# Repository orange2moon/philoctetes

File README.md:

# Philoctetes Keyboard

## About this project

I have worked on this project for about 3 months. It is quite enjoyable, but also time consuming. I made two working keyboards, one bluetooth and one wireless. The feel of the layout is fantastic! Even if my keyboards are working, it's not ready for other people to build. I hope to have time to continue this project, but I can't make promises to anyone. I am sharing this repository for people who might be curious, and to give ideas so as to inspire people to make awesome keyboards.

__Design goals__  
In [congnitive load theory](https://practicalpie.com/cognitive-load-theory/) there are three processes. These are the intrinsic, the extrinsic, and the germane. The effort put into typing on a keyboard is purely extrinsic. So one day I had an idea, "could I reduce the extrinsic load of typing on a computer by changing my keyboard?". I think the answer is yes. As a result of this idea, my design goals gravitated toward 42 keys that are arranged to match my hand and the movements of my fingers.

This keyboard turned into a very expensive build. It is probably one of the most expensive split keyboards you can build. In addition I only considered the shape and size of my own hand when designing it. Please don't build it.

## Other Projects to Check Out

The [Totem](https://github.com/GEIGEIGEIST/TOTEM) keyboard. The Totem was the inspiration for this keyboard. I have huge respect for the creator of this project. The creator really put a lot of effort into making a great finished project.

I created this project with a different design goal in mind. The design goals of the Totem seem to be a portable and relativly low cost keyboard. In contrast, my design goals are to fit perfectly my own hand.

In addition, a big thanks to the [EIGA](https://www.youtube.com/@EIGAtech) youtube channel. Without their channel I would not have learned about the Totem and other split keyboards.

## To Do

__Case__  
[x] Add a case mount point to the far outside.  
[x] Add more space for the oled (the oled is not centered and it hits the lip holding the cover). Moving the oled mount half a mm towards the edge should help.  
[x] Add more space for the microcontroller (about 1mm on the inner side should do).  
[x] Add a curve for the TRRS conector.  

__PCB Both Sides__  
[x] fix the annotations  
[] change the footprints from sod-323 to sod-123.  
    - The Kicad library footprints look too small for hand soldering.  
[] Update the footprints in the PCB builder.  
[] Redo diode placement  
[] Redo routing  
[] Improve the silkscreen placements.  
[x] Improve the placement of the oled display.  
[x] Add a case mount point to the far outside.  
[x] Add a pull down resistor to the right side.  
[x] Remove the extra diode on the left side.  
[x] Panelize the keyboard.  
[x] Check the column and row labels and makes sure they match.  
[x] Check the oled and nice!view pinouts.  
  
__Project In General__  
[] Create a bill of materials  
[] Create a build guide  
[] Test latest PCB  
  
## Case  
  
The case uses a tenting system that I have used for a year. It's not perfect, but every-time I think of switching to a different design I can't find justification. The advantage of my tenting system is that it is very stable and very adjustable. My tenting system is not portable, meaning it will probably bet messed up if you put it in a bag and ride the subway (been there, done that).  
  
The case was designed using onshape and you can find a link to it [here](https://cad.onshape.com/documents/5c5e04ae1784123d6189c14c/w/86f29d74e9109abb974cb649/e/b3c51a35815c88e0a251e0eb?renderMode=0&uiState=679c96c15b955f7398b0b3b0)  

## Images

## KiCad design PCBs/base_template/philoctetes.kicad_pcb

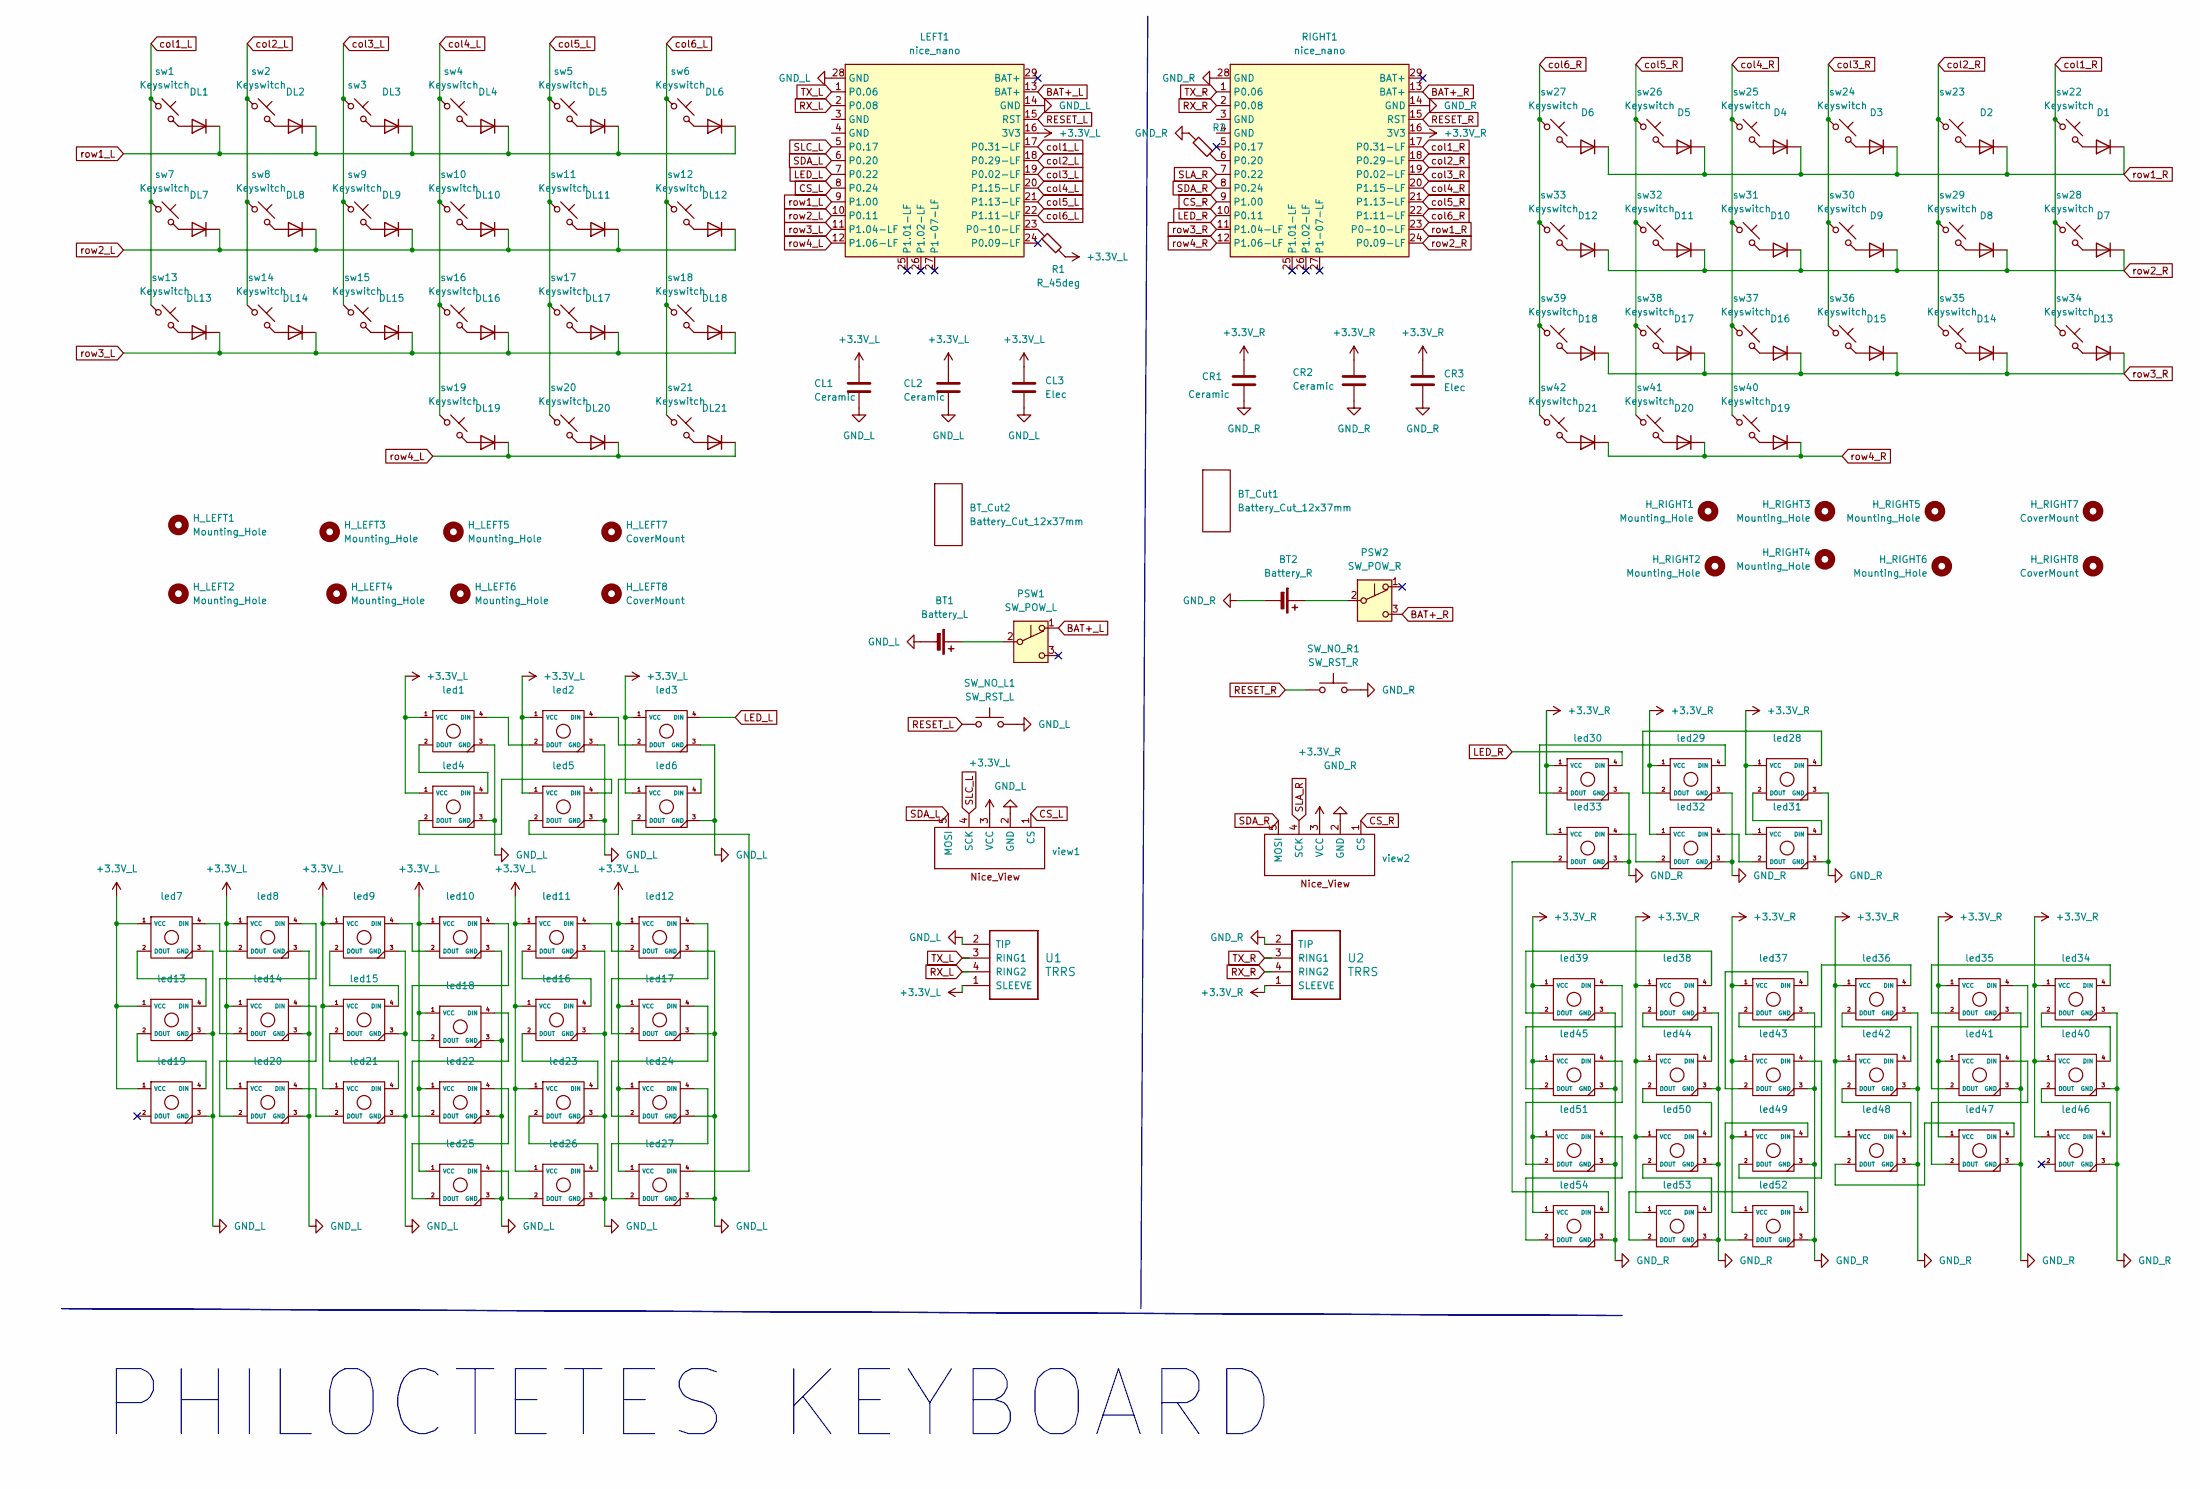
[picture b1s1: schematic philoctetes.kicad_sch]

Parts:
BT1: Battery_L; JST_GH_SM02B-GHS-TB_1x02-1MP_P1.25mm_Horizontal
BT2: Battery_R; JST_GH_SM02B-GHS-TB_1x02-1MP_P1.25mm_Horizontal
BT_Cut1, BT_Cut2: Battery_Cut_12x37mm
CL1, CL2: Ceramic; C_1206_3216Metric_Pad1.33x1.80mm_HandSolder
CL3: Elec; CP_Radial_D5.0mm_P2.00mm
CR1, CR2: Ceramic; C_1206_3216Metric_Pad1.33x1.80mm_HandSolder
CR3: Elec; CP_Radial_D5.0mm_P2.00mm
D1, D2, D3, D4, D5, D6, D7, D8, D9, D10, D11, D12, D13, D14, D15, D16, D17, D18, D19, D20, D21: 1N4148W; D_SOD-123F
DL1, DL2, DL3, DL4, DL5, DL6, DL7, DL8, DL9, DL10, DL11, DL12, DL13, DL14, DL15, DL16, DL17, DL18, DL19, DL20, DL21: 1N4148W; D_SOD-123F
H_LEFT1, H_LEFT2, H_LEFT3, H_LEFT4, H_LEFT5, H_LEFT6: Mounting_Hole; MountingHole_3.2mm_M3_DIN965
H_LEFT7, H_LEFT8: CoverMount; MountingHole_2.2mm_M2_Pad
H_RIGHT1, H_RIGHT2, H_RIGHT3, H_RIGHT4, H_RIGHT5, H_RIGHT6: Mounting_Hole; MountingHole_3.2mm_M3_DIN965
H_RIGHT7, H_RIGHT8: CoverMount; MountingHole_2.2mm_M2_Pad
LEFT1: nice_nano; nice_nano_AH_USBup
PSW1: SW_POW_L; MSK12C02
PSW2: SW_POW_R; MSK12C02
R1, R2: R_45deg; R_0805_2012Metric
RIGHT1: nice_nano; nice_nano_AH_USBup
SW_NO_L1: SW_RST_L; SW_RST
SW_NO_R1: SW_RST_R; SW_RST
U1, U2: TRRS; TRRS_PJ-320A
led1, led2, led3, led4, led5, led6, led28, led29, led30, led31, led32, led33: LED_SK6812MINI-E_faceup
led7, led8, led9, led10, led11, led12, led13, led14, led15, led16, led17, led18, led19, led20, led21, led22, led23, led24, led25, led26, led27, led34, led35, led36, led37, led38, led39, led40, led41, led42, led43, led44, led45, led46, led47, led48, led49, led50, led51, led52, led53, led54: LED_SK6812MINI-E_facedown
sw1, sw2, sw3, sw4, sw5, sw6, sw7, sw8, sw9, sw10, sw11, sw12, sw13, sw14, sw15, sw16, sw17, sw18, sw19, sw20, sw21, sw22, sw23, sw24, sw25, sw26, sw27, sw28, sw29, sw30, sw31, sw32, sw33, sw34, sw35, sw36, sw37, sw38, sw39, sw40, sw41, sw42: Keyswitch; Hotswap_Choc_V1V2_1.00u
view1, view2: nice_view

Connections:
+3.3V_L: CL1.1, CL2.1, CL3.1, LEFT1.16 (3V3), R1.2, U1.1 (SLEEVE), led1.1 (VCC), led2.1 (VCC), led3.1 (VCC), led4.1 (VCC), led5.1 (VCC), led6.1 (VCC), led7.1 (VCC), led8.1 (VCC), led9.1 (VCC), led10.1 (VCC), led11.1 (VCC), led12.1 (VCC), led13.1 (VCC), led14.1 (VCC), led15.1 (VCC), led16.1 (VCC), led17.1 (VCC), led18.1 (VCC), led19.1 (VCC), led20.1 (VCC), led21.1 (VCC), led22.1 (VCC), led23.1 (VCC), led24.1 (VCC), led25.1 (VCC), led26.1 (VCC), led27.1 (VCC), view1.3 (VCC)
+3.3V_R: CR1.1, CR2.1, CR3.1, RIGHT1.16 (3V3), U2.1 (SLEEVE), led28.1 (VCC), led29.1 (VCC), led30.1 (VCC), led31.1 (VCC), led32.1 (VCC), led33.1 (VCC), led34.1 (VCC), led35.1 (VCC), led36.1 (VCC), led37.1 (VCC), led38.1 (VCC), led39.1 (VCC), led40.1 (VCC), led41.1 (VCC), led42.1 (VCC), led43.1 (VCC), led44.1 (VCC), led45.1 (VCC), led46.1 (VCC), led47.1 (VCC), led48.1 (VCC), led49.1 (VCC), led50.1 (VCC), led51.1 (VCC), led52.1 (VCC), led53.1 (VCC), led54.1 (VCC), view2.3 (VCC)
BAT+_L: LEFT1.13 (BAT+), PSW1.1 (A)
BAT+_R: PSW2.3 (C), RIGHT1.13 (BAT+)
CS_L: LEFT1.8 (P0.24), view1.1 (CS)
CS_R: RIGHT1.9 (P1.00), view2.1 (CS)
GND_L: BT1.2 (-), CL1.2, CL2.2, CL3.2, LEFT1.14 (GND), LEFT1.28 (GND), SW_NO_L1.2, U1.2 (TIP), led1.3 (GND), led2.3 (GND), led3.3 (GND), led4.3 (GND), led5.3 (GND), led6.3 (GND), led7.3 (GND), led8.3 (GND), led9.3 (GND), led10.3 (GND), led11.3 (GND), led12.3 (GND), led13.3 (GND), led14.3 (GND), led15.3 (GND), led16.3 (GND), led17.3 (GND), led18.3 (GND), led19.3 (GND), led20.3 (GND), led21.3 (GND), led22.3 (GND), led23.3 (GND), led24.3 (GND), led25.3 (GND), led26.3 (GND), led27.3 (GND), view1.2 (GND)
GND_R: BT2.2 (-), CR1.2, CR2.2, CR3.2, R2.2, RIGHT1.14 (GND), RIGHT1.28 (GND), SW_NO_R1.2, U2.2 (TIP), led28.3 (GND), led29.3 (GND), led30.3 (GND), led31.3 (GND), led32.3 (GND), led33.3 (GND), led34.3 (GND), led35.3 (GND), led36.3 (GND), led37.3 (GND), led38.3 (GND), led39.3 (GND), led40.3 (GND), led41.3 (GND), led42.3 (GND), led43.3 (GND), led44.3 (GND), led45.3 (GND), led46.3 (GND), led47.3 (GND), led48.3 (GND), led49.3 (GND), led50.3 (GND), led51.3 (GND), led52.3 (GND), led53.3 (GND), led54.3 (GND), view2.2 (GND)
LED_L: LEFT1.7 (P0.22), led3.4 (DIN)
LED_R: RIGHT1.10 (P0.11), led30.4 (DIN)
unnamed: BT1.1 (+), PSW1.2 (B)
unnamed: BT2.1 (+), PSW2.2 (B)
unnamed: D1.2 (A), sw22.2
unnamed: D2.2 (A), sw23.2
unnamed: D3.2 (A), sw24.2
unnamed: D4.2 (A), sw25.2
unnamed: D5.2 (A), sw26.2
unnamed: D6.2 (A), sw27.2
unnamed: D7.2 (A), sw28.2
unnamed: D8.2 (A), sw29.2
unnamed: D9.2 (A), sw30.2
unnamed: D10.2 (A), sw31.2
unnamed: D11.2 (A), sw32.2
unnamed: D12.2 (A), sw33.2
unnamed: D13.2 (A), sw34.2
unnamed: D14.2 (A), sw35.2
unnamed: D15.2 (A), sw36.2
unnamed: D16.2 (A), sw37.2
unnamed: D17.2 (A), sw38.2
unnamed: D18.2 (A), sw39.2
unnamed: D19.2 (A), sw40.2
unnamed: D20.2 (A), sw41.2
unnamed: D21.2 (A), sw42.2
unnamed: DL1.2 (A), sw1.2
unnamed: DL2.2 (A), sw2.2
unnamed: DL3.2 (A), sw3.2
unnamed: DL4.2 (A), sw4.2
unnamed: DL5.2 (A), sw5.2
unnamed: DL6.2 (A), sw6.2
unnamed: DL7.2 (A), sw7.2
unnamed: DL8.2 (A), sw8.2
unnamed: DL9.2 (A), sw9.2
unnamed: DL10.2 (A), sw10.2
unnamed: DL11.2 (A), sw11.2
unnamed: DL12.2 (A), sw12.2
unnamed: DL13.2 (A), sw13.2
unnamed: DL14.2 (A), sw14.2
unnamed: DL15.2 (A), sw15.2
unnamed: DL16.2 (A), sw16.2
unnamed: DL17.2 (A), sw17.2
unnamed: DL18.2 (A), sw18.2
unnamed: DL19.2 (A), sw19.2
unnamed: DL20.2 (A), sw20.2
unnamed: DL21.2 (A), sw21.2
unnamed: LEFT1.23 (P0-10-LF), R1.1
unnamed: R2.1, RIGHT1.6 (P0.20)
unnamed: led1.4 (DIN), led2.2 (DOUT)
unnamed: led1.2 (DOUT), led4.4 (DIN)
unnamed: led2.4 (DIN), led3.2 (DOUT)
unnamed: led4.2 (DOUT), led5.4 (DIN)
unnamed: led5.2 (DOUT), led6.4 (DIN)
unnamed: led7.4 (DIN), led8.2 (DOUT)
unnamed: led10.4 (DIN), led18.2 (DOUT)
unnamed: led9.4 (DIN), led10.2 (DOUT)
unnamed: led11.4 (DIN), led12.2 (DOUT)
unnamed: led11.2 (DOUT), led16.4 (DIN)
unnamed: led12.4 (DIN), led17.2 (DOUT)
unnamed: led7.2 (DOUT), led13.4 (DIN)
unnamed: led13.2 (DOUT), led19.4 (DIN)
unnamed: led14.4 (DIN), led20.2 (DOUT)
unnamed: led8.4 (DIN), led14.2 (DOUT)
unnamed: led9.2 (DOUT), led15.4 (DIN)
unnamed: led15.2 (DOUT), led21.4 (DIN)
unnamed: led16.2 (DOUT), led23.4 (DIN)
unnamed: led17.4 (DIN), led24.2 (DOUT)
unnamed: led18.4 (DIN), led22.2 (DOUT)
unnamed: led20.4 (DIN), led21.2 (DOUT)
unnamed: led22.4 (DIN), led25.2 (DOUT)
unnamed: led23.2 (DOUT), led26.4 (DIN)
unnamed: led24.4 (DIN), led27.2 (DOUT)
unnamed: led25.4 (DIN), led26.2 (DOUT)
unnamed: led6.2 (DOUT), led27.4 (DIN)
unnamed: led28.4 (DIN), led29.2 (DOUT)
unnamed: led28.2 (DOUT), led31.4 (DIN)
unnamed: led29.4 (DIN), led30.2 (DOUT)
unnamed: led31.2 (DOUT), led32.4 (DIN)
unnamed: led32.2 (DOUT), led33.4 (DIN)
unnamed: led33.2 (DOUT), led54.4 (DIN)
unnamed: led34.4 (DIN), led35.2 (DOUT)
unnamed: led34.2 (DOUT), led40.4 (DIN)
unnamed: led35.4 (DIN), led41.2 (DOUT)
unnamed: led36.4 (DIN), led37.2 (DOUT)
unnamed: led36.2 (DOUT), led42.4 (DIN)
unnamed: led37.4 (DIN), led43.2 (DOUT)
unnamed: led38.4 (DIN), led39.2 (DOUT)
unnamed: led38.2 (DOUT), led44.4 (DIN)
unnamed: led39.4 (DIN), led45.2 (DOUT)
unnamed: led40.2 (DOUT), led46.4 (DIN)
unnamed: led41.4 (DIN), led47.2 (DOUT)
unnamed: led42.2 (DOUT), led48.4 (DIN)
unnamed: led43.4 (DIN), led49.2 (DOUT)
unnamed: led44.2 (DOUT), led50.4 (DIN)
unnamed: led45.4 (DIN), led51.2 (DOUT)
unnamed: led47.4 (DIN), led48.2 (DOUT)
unnamed: led49.4 (DIN), led52.2 (DOUT)
unnamed: led50.2 (DOUT), led53.4 (DIN)
unnamed: led51.4 (DIN), led54.2 (DOUT)
unnamed: led52.4 (DIN), led53.2 (DOUT)
RESET_L: LEFT1.15 (RST), SW_NO_L1.1
RESET_R: RIGHT1.15 (RST), SW_NO_R1.1
RX_L: LEFT1.2 (P0.08), U1.4 (RING2)
RX_R: RIGHT1.2 (P0.08), U2.4 (RING2)
SDA_L: LEFT1.6 (P0.20), view1.5 (MOSI)
SDA_R: RIGHT1.8 (P0.24), view2.5 (MOSI)
SLA_R: RIGHT1.7 (P0.22), view2.4 (SCK)
SLC_L: LEFT1.5 (P0.17), view1.4 (SCK)
TX_L: LEFT1.1 (P0.06), U1.3 (RING1)
TX_R: RIGHT1.1 (P0.06), U2.3 (RING1)
col1_L: LEFT1.17 (P0.31-LF), sw1.1, sw7.1, sw13.1
col1_R: RIGHT1.17 (P0.31-LF), sw22.1, sw28.1, sw34.1
col2_L: LEFT1.18 (P0.29-LF), sw2.1, sw8.1, sw14.1
col2_R: RIGHT1.18 (P0.29-LF), sw23.1, sw29.1, sw35.1
col3_L: LEFT1.19 (P0.02-LF), sw3.1, sw9.1, sw15.1
col3_R: RIGHT1.19 (P0.02-LF), sw24.1, sw30.1, sw36.1
col4_L: LEFT1.20 (P1.15-LF), sw4.1, sw10.1, sw16.1, sw19.1
col4_R: RIGHT1.20 (P1.15-LF), sw25.1, sw31.1, sw37.1, sw40.1
col5_L: LEFT1.21 (P1.13-LF), sw5.1, sw11.1, sw17.1, sw20.1
col5_R: RIGHT1.21 (P1.13-LF), sw26.1, sw32.1, sw38.1, sw41.1
col6_L: LEFT1.22 (P1.11-LF), sw6.1, sw12.1, sw18.1, sw21.1
col6_R: RIGHT1.22 (P1.11-LF), sw27.1, sw33.1, sw39.1, sw42.1
row1_L: DL1.1 (K), DL2.1 (K), DL3.1 (K), DL4.1 (K), DL5.1 (K), DL6.1 (K), LEFT1.9 (P1.00)
row1_R: D1.1 (K), D2.1 (K), D3.1 (K), D4.1 (K), D5.1 (K), D6.1 (K), RIGHT1.23 (P0-10-LF)
row2_L: DL7.1 (K), DL8.1 (K), DL9.1 (K), DL10.1 (K), DL11.1 (K), DL12.1 (K), LEFT1.10 (P0.11)
row2_R: D7.1 (K), D8.1 (K), D9.1 (K), D10.1 (K), D11.1 (K), D12.1 (K), RIGHT1.24 (P0.09-LF)
row3_L: DL13.1 (K), DL14.1 (K), DL15.1 (K), DL16.1 (K), DL17.1 (K), DL18.1 (K), LEFT1.11 (P1.04-LF)
row3_R: D13.1 (K), D14.1 (K), D15.1 (K), D16.1 (K), D17.1 (K), D18.1 (K), RIGHT1.11 (P1.04-LF)
row4_L: DL19.1 (K), DL20.1 (K), DL21.1 (K), LEFT1.12 (P1.06-LF)
row4_R: D19.1 (K), D20.1 (K), D21.1 (K), RIGHT1.12 (P1.06-LF)

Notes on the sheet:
PHILOCTETES KEYBOARD

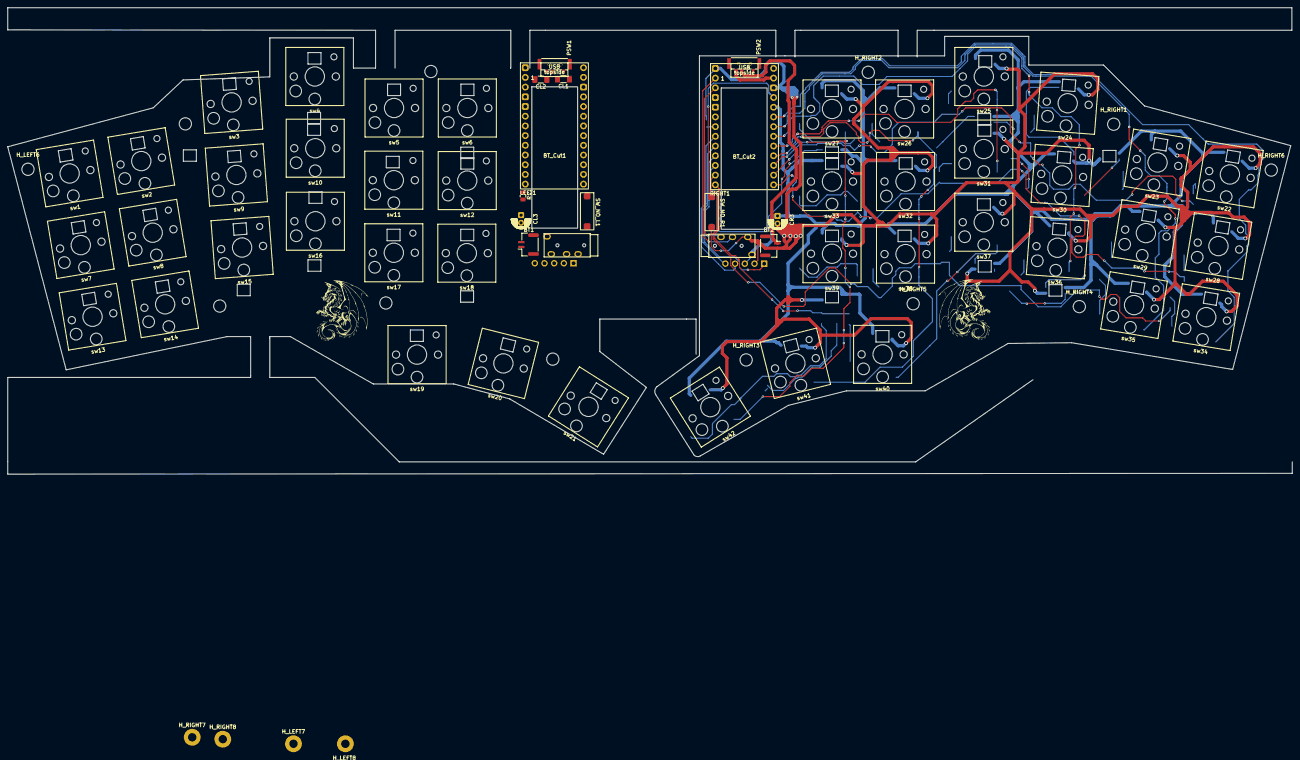
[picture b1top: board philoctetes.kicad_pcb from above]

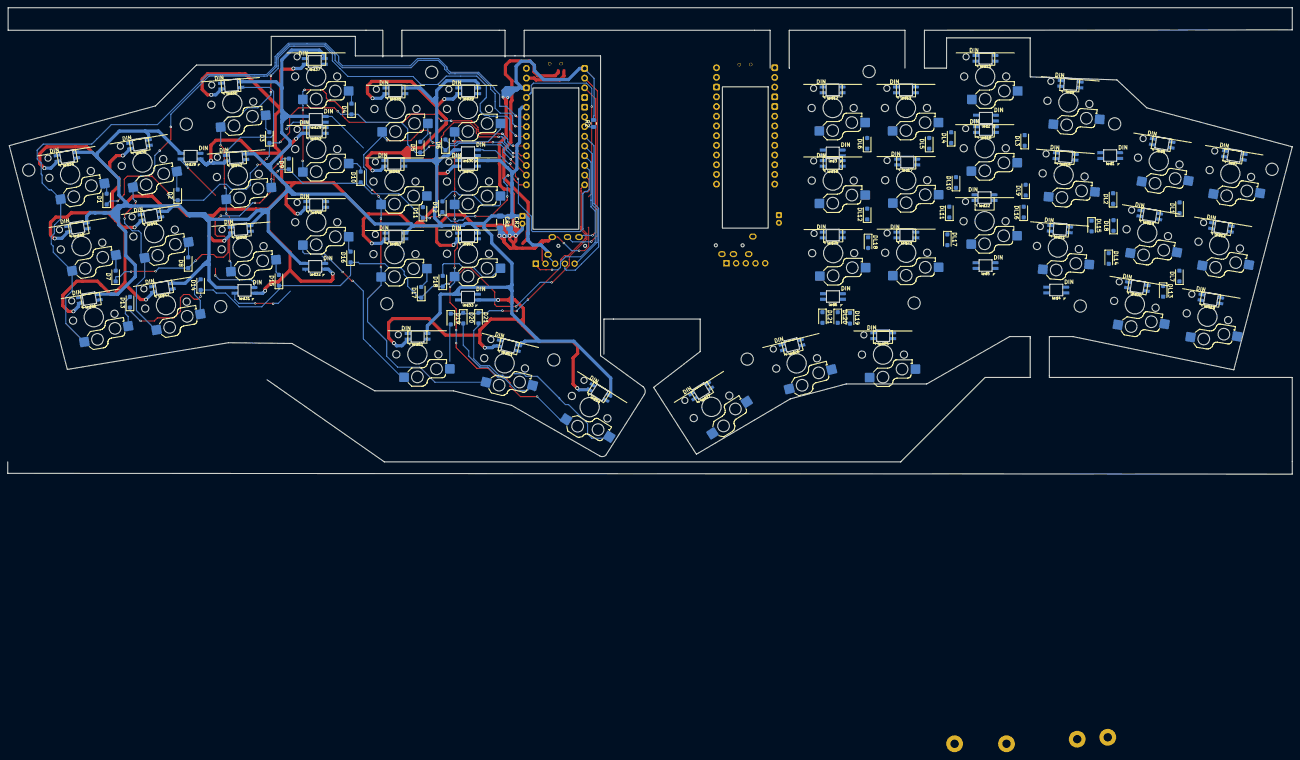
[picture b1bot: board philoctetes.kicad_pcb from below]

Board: 2 copper layers, 336.3 x 122.1 mm, 176 parts (45 on the bottom side), 138 nets.

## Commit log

2025-01-31 repo creation
2025-01-31 basic board setup
2025-01-31 added case files
2025-01-31 todo list
2025-01-31 formatting
2025-01-31 image
2025-01-31 image..
2025-01-31 picture
2025-01-31 picture comment
2025-01-31 to do list
2025-01-31 to do list...
2025-01-31 comment
2025-01-31 edit
2025-01-31 layout pdf for printing
2025-02-01 updates annotations
2025-02-02 at home layout tester
2025-02-02 work in progress
2025-08-02 organization
2025-08-06 layout right side improvements
2025-08-07 working on routing
2025-08-07 routing right half; diodes, power, reset, tx, rx, clk...
2025-08-09 worked on edge cuts, made freecad, mirrored, imported to kicad
2025-08-10 Finished routing and edge cuts, next up.. check for mistakes.
2025-08-10 fixed some routing mistakes, added some clearance for tx/rx, added per led 1nf capacitors (needs to place footprints)
2025-08-12 placed all 1NF capacitors
2025-08-12 rotary encoder considerations

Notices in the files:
PCBs/base_template/philoctetes.kicad_sch:
License: CERN-OHL-S
